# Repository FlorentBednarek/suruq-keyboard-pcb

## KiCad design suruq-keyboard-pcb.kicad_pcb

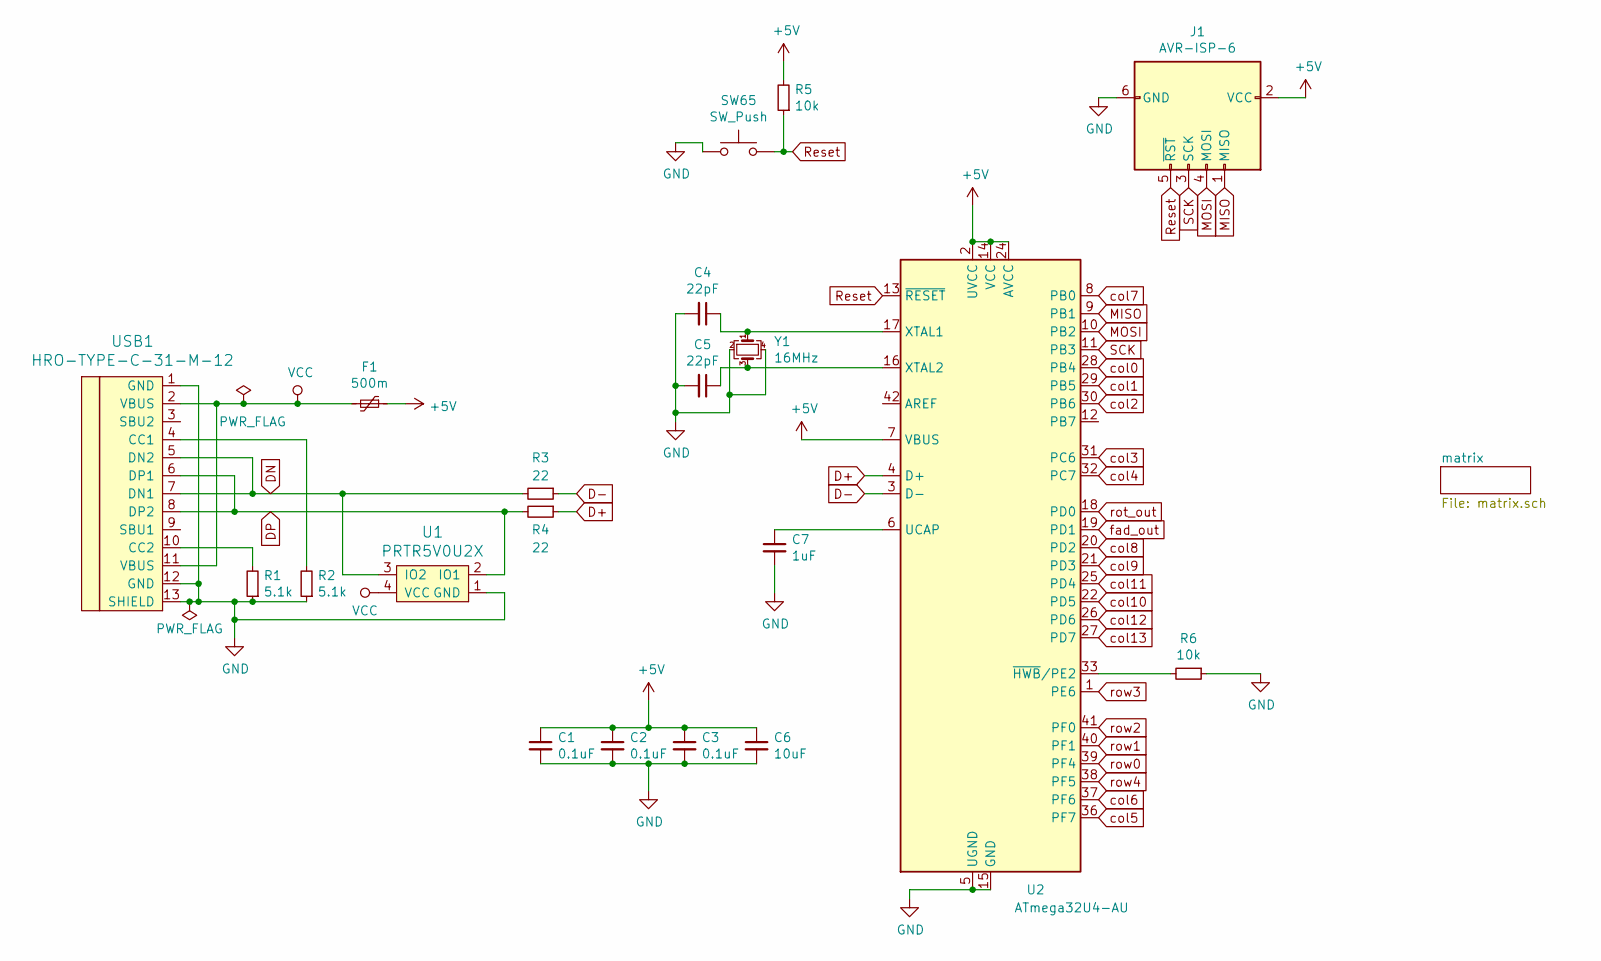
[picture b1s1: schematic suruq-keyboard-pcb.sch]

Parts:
C1, C2, C3: 0.1uF; C_0805_2012Metric_Pad1.15x1.40mm_HandSolder
C4, C5: 22pF; C_0805_2012Metric_Pad1.15x1.40mm_HandSolder
C6: 10uF; C_0805_2012Metric_Pad1.15x1.40mm_HandSolder
C7: 1uF; C_0805_2012Metric_Pad1.15x1.40mm_HandSolder
F1: 500m; Fuse_1206_3216Metric_Pad1.42x1.75mm_HandSolder
J1: AVR-ISP-6; Reset_Pretty-Mask
R1, R2: 5.1k; R_0805_2012Metric_Pad1.15x1.40mm_HandSolder
R3, R4: 22; R_0805_2012Metric_Pad1.15x1.40mm_HandSolder
R5, R6: 10k; R_0805_2012Metric_Pad1.15x1.40mm_HandSolder
SW65: SW_Push; SW_SPST_SKQG_WithStem
U1: PRTR5V0U2X; SOT143B
U2: ATmega32U4-AU; TQFP-44_10x10mm_P0.8mm
USB1: HRO-TYPE-C-31-M-12; HRO-TYPE-C-31-M-12-HandSoldering
Y1: 16MHz; Crystal_SMD_3225-4Pin_3.2x2.5mm_HandSoldering

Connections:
+5V: C1.1, C2.1, C3.1, C6.1, F1.1, J1.2 (VCC), R5.2, U2.2 (UVCC), U2.7 (VBUS), U2.14 (VCC), U2.24 (AVCC), U2.34 (VCC), U2.44 (AVCC); also elsewhere on the board
D+: R4.1, U2.4 (D+)
D-: R3.1, U2.3 (D-)
DN: R3.2, U1.3 (IO2), USB1.5 (DN2), USB1.7 (DN1)
DP: R4.2, U1.2 (IO1), USB1.6 (DP1), USB1.8 (DP2)
GND: C1.2, C2.2, C3.2, C4.2, C5.2, C6.2, C7.2, J1.6 (GND), R1.1, R2.1, R6.1, SW65.1, U1.1 (GND), U2.5 (UGND), U2.15 (GND), U2.23 (GND), U2.35 (GND), U2.43 (GND), USB1.1 (GND), USB1.12 (GND), USB1.13 (SHIELD), Y1.2, Y1.4; also elsewhere on the board
MISO: J1.1 (MISO), U2.9 (PB1)
MOSI: J1.4 (MOSI), U2.10 (PB2)
unnamed: C4.1, U2.17 (XTAL1), Y1.1
unnamed: C5.1, U2.16 (XTAL2), Y1.3
unnamed: C7.1, U2.6 (UCAP)
unnamed: R1.2, USB1.10 (CC2)
unnamed: R2.2, USB1.4 (CC1)
unnamed: R6.2, U2.33 (~HWB~/PE2)
Reset: J1.5 (~RST), R5.1, SW65.2, U2.13 (~RESET)
SCK: J1.3 (SCK), U2.11 (PB3)
VCC: F1.2, U1.4 (VCC), USB1.2 (VBUS), USB1.11 (VBUS)
col0: U2.28 (PB4); also elsewhere on the board
col1: U2.29 (PB5); also elsewhere on the board
col2: U2.30 (PB6); also elsewhere on the board
col3: U2.31 (PC6); also elsewhere on the board
col4: U2.32 (PC7); also elsewhere on the board
col5: U2.36 (PF7); also elsewhere on the board
col6: U2.37 (PF6); also elsewhere on the board
col7: U2.8 (PB0); also elsewhere on the board
col8: U2.20 (PD2); also elsewhere on the board
col9: U2.21 (PD3); also elsewhere on the board
col10: U2.22 (PD5); also elsewhere on the board
col11: U2.25 (PD4); also elsewhere on the board
col12: U2.26 (PD6); also elsewhere on the board
col13: U2.27 (PD7); also elsewhere on the board
fad_out: U2.19 (PD1); also elsewhere on the board
rot_out: U2.18 (PD0); also elsewhere on the board
row0: U2.39 (PF4); also elsewhere on the board
row1: U2.40 (PF1); also elsewhere on the board
row2: U2.41 (PF0); also elsewhere on the board
row3: U2.1 (PE6); also elsewhere on the board
row4: U2.38 (PF5); also elsewhere on the board

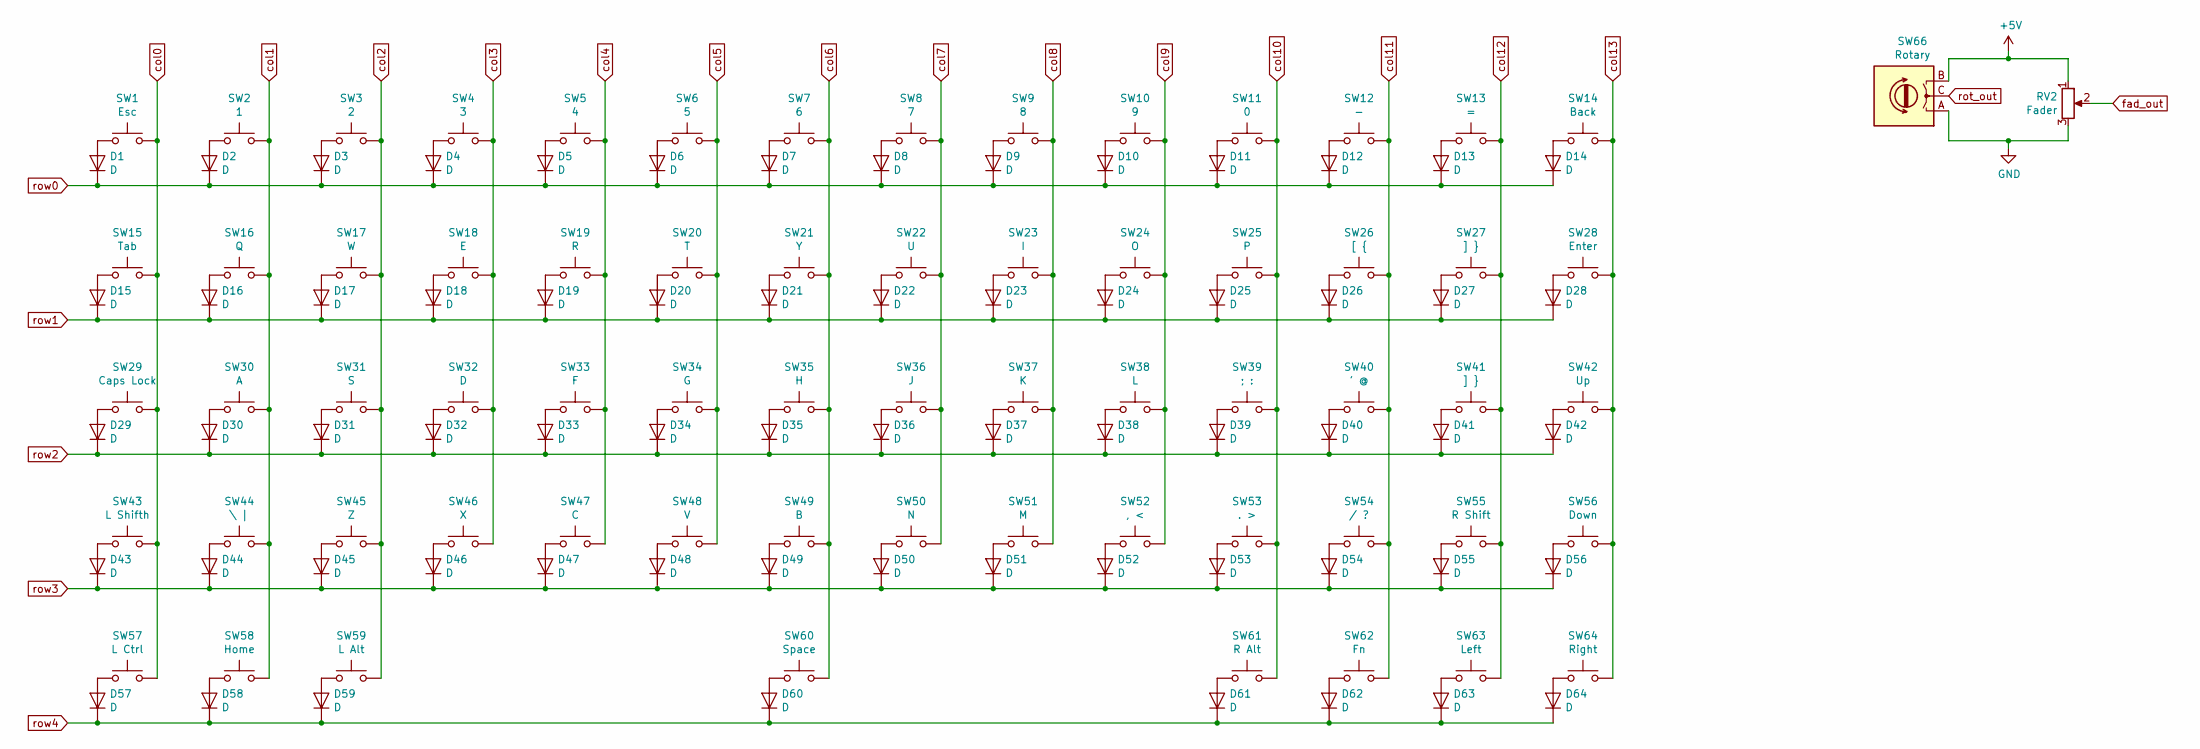
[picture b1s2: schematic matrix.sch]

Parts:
D1, D2, D3, D4, D5, D6, D7, D8, D9, D10, D11, D12, D13, D14, D15, D16, D17, D18, D19, D20, D21, D22, D23, D24, D25, D26, D27, D28, D29, D30, D31, D32, D33, D34, D35, D36, D37, D38, D39, D40, D41, D42, D43, D44, D45, D46, D47, D48, D49, D50, D51, D52, D53, D54, D55, D56, D57, D58, D59, D60, D61, D62, D63, D64: D; D_SOD-123
RV2: Fader; Potentiometer_Bourns_PTA4543_Single_Slide
SW1: Esc; SW_Cherry_MX_1.00u_PCB_NameSilk
SW2: 1; SW_Cherry_MX_1.00u_PCB_NameSilk
SW3: 2; SW_Cherry_MX_1.00u_PCB_NameSilk
SW4: 3; SW_Cherry_MX_1.00u_PCB_NameSilk
SW5: 4; SW_Cherry_MX_1.00u_PCB_NameSilk
SW6: 5; SW_Cherry_MX_1.00u_PCB_NameSilk
SW7: 6; SW_Cherry_MX_1.00u_PCB_NameSilk
SW8: 7; SW_Cherry_MX_1.00u_PCB_NameSilk
SW9: 8; SW_Cherry_MX_1.00u_PCB_NameSilk
SW10: 9; SW_Cherry_MX_1.00u_PCB_NameSilk
SW11: 0; SW_Cherry_MX_1.00u_PCB_NameSilk
SW12: -; SW_Cherry_MX_1.00u_PCB_NameSilk
SW13: =; SW_Cherry_MX_1.00u_PCB_NameSilk
SW14: Back; SW_Cherry_MX_2.00u_PCB_NameSilk
SW15: Tab; SW_Cherry_MX_1.50u_PCB_NameSilk
SW16: Q; SW_Cherry_MX_1.00u_PCB_NameSilk
SW17: W; SW_Cherry_MX_1.00u_PCB_NameSilk
SW18: E; SW_Cherry_MX_1.00u_PCB_NameSilk
SW19: R; SW_Cherry_MX_1.00u_PCB_NameSilk
SW20: T; SW_Cherry_MX_1.00u_PCB_NameSilk
SW21: Y; SW_Cherry_MX_1.00u_PCB_NameSilk
SW22: U; SW_Cherry_MX_1.00u_PCB_NameSilk
SW23: I; SW_Cherry_MX_1.00u_PCB_NameSilk
SW24: O; SW_Cherry_MX_1.00u_PCB_NameSilk
SW25: P; SW_Cherry_MX_1.00u_PCB_NameSilk
SW26: [ {; SW_Cherry_MX_1.00u_PCB_NameSilk
SW27, SW41: ] }; SW_Cherry_MX_1.00u_PCB_NameSilk
SW28: Enter; SW_Cherry_MX_ISOEnter_PCB_NameSilk
SW29: Caps Lock; SW_Cherry_MX_1.75u_PCB_NameSilk
SW30: A; SW_Cherry_MX_1.00u_PCB_NameSilk
SW31: S; SW_Cherry_MX_1.00u_PCB_NameSilk
SW32: D; SW_Cherry_MX_1.00u_PCB_NameSilk
SW33: F; SW_Cherry_MX_1.00u_PCB_NameSilk
SW34: G; SW_Cherry_MX_1.00u_PCB_NameSilk
SW35: H; SW_Cherry_MX_1.00u_PCB_NameSilk
SW36: J; SW_Cherry_MX_1.00u_PCB_NameSilk
SW37: K; SW_Cherry_MX_1.00u_PCB_NameSilk
SW38: L; SW_Cherry_MX_1.00u_PCB_NameSilk
SW39: ; :; SW_Cherry_MX_1.00u_PCB_NameSilk
SW40: ' @; SW_Cherry_MX_1.00u_PCB_NameSilk
SW42: Up; SW_Cherry_MX_1.00u_PCB_NameSilk
SW43: L Shifth; SW_Cherry_MX_1.25u_PCB_NameSilk
SW44: \\ |; SW_Cherry_MX_1.00u_PCB_NameSilk
SW45: Z; SW_Cherry_MX_1.00u_PCB_NameSilk
SW46: X; SW_Cherry_MX_1.00u_PCB_NameSilk
SW47: C; SW_Cherry_MX_1.00u_PCB_NameSilk
SW48: V; SW_Cherry_MX_1.00u_PCB_NameSilk
SW49: B; SW_Cherry_MX_1.00u_PCB_NameSilk
SW50: N; SW_Cherry_MX_1.00u_PCB_NameSilk
SW51: M; SW_Cherry_MX_1.00u_PCB_NameSilk
SW52: , <; SW_Cherry_MX_1.00u_PCB_NameSilk
SW53: . >; SW_Cherry_MX_1.00u_PCB_NameSilk
SW54: / ?; SW_Cherry_MX_1.00u_PCB_NameSilk
SW55: R Shift; SW_Cherry_MX_1.75u_PCB_NameSilk
SW56: Down; SW_Cherry_MX_1.00u_PCB_NameSilk
SW57: L Ctrl; SW_Cherry_MX_1.25u_PCB_NameSilk
SW58: Home; SW_Cherry_MX_1.25u_PCB_NameSilk
SW59: L Alt; SW_Cherry_MX_1.25u_PCB_NameSilk
SW60: Space; SW_Cherry_MX_6.25u_PCB_NameSilk
SW61: R Alt; SW_Cherry_MX_1.50u_PCB_NameSilk
SW62: Fn; SW_Cherry_MX_1.50u_PCB_NameSilk
SW63: Left; SW_Cherry_MX_1.00u_PCB_NameSilk
SW64: Right; SW_Cherry_MX_1.00u_PCB_NameSilk
SW66: Rotary; RotaryEncoder_Alps_EC11E_Vertical_H20mm

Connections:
+5V: RV2.1, SW66.B; also elsewhere on the board
GND: RV2.3, SW66.A; also elsewhere on the board
unnamed: D1.2 (A), SW1.1
unnamed: D2.2 (A), SW2.1
unnamed: D3.2 (A), SW3.1
unnamed: D4.2 (A), SW4.1
unnamed: D5.2 (A), SW5.1
unnamed: D6.2 (A), SW6.1
unnamed: D7.2 (A), SW7.1
unnamed: D8.2 (A), SW8.1
unnamed: D9.2 (A), SW9.1
unnamed: D10.2 (A), SW10.1
unnamed: D11.2 (A), SW11.1
unnamed: D12.2 (A), SW12.1
unnamed: D13.2 (A), SW13.1
unnamed: D14.2 (A), SW14.1
unnamed: D15.2 (A), SW15.1
unnamed: D16.2 (A), SW16.1
unnamed: D17.2 (A), SW17.1
unnamed: D18.2 (A), SW18.1
unnamed: D19.2 (A), SW19.1
unnamed: D20.2 (A), SW20.1
unnamed: D21.2 (A), SW21.1
unnamed: D22.2 (A), SW22.1
unnamed: D23.2 (A), SW23.1
unnamed: D24.2 (A), SW24.1
unnamed: D25.2 (A), SW25.1
unnamed: D26.2 (A), SW26.1
unnamed: D27.2 (A), SW27.1
unnamed: D28.2 (A), SW28.1
unnamed: D29.2 (A), SW29.1
unnamed: D30.2 (A), SW30.1
unnamed: D31.2 (A), SW31.1
unnamed: D32.2 (A), SW32.1
unnamed: D33.2 (A), SW33.1
unnamed: D34.2 (A), SW34.1
unnamed: D35.2 (A), SW35.1
unnamed: D36.2 (A), SW36.1
unnamed: D37.2 (A), SW37.1
unnamed: D38.2 (A), SW38.1
unnamed: D39.2 (A), SW39.1
unnamed: D40.2 (A), SW40.1
unnamed: D41.2 (A), SW41.1
unnamed: D42.2 (A), SW42.1
unnamed: D43.2 (A), SW43.1
unnamed: D44.2 (A), SW44.1
unnamed: D45.2 (A), SW45.1
unnamed: D46.2 (A), SW46.1
unnamed: D47.2 (A), SW47.1
unnamed: D48.2 (A), SW48.1
unnamed: D49.2 (A), SW49.1
unnamed: D50.2 (A), SW50.1
unnamed: D51.2 (A), SW51.1
unnamed: D52.2 (A), SW52.1
unnamed: D53.2 (A), SW53.1
unnamed: D54.2 (A), SW54.1
unnamed: D55.2 (A), SW55.1
unnamed: D56.2 (A), SW56.1
unnamed: D57.2 (A), SW57.1
unnamed: D58.2 (A), SW58.1
unnamed: D59.2 (A), SW59.1
unnamed: D60.2 (A), SW60.1
unnamed: D61.2 (A), SW61.1
unnamed: D62.2 (A), SW62.1
unnamed: D63.2 (A), SW63.1
unnamed: D64.2 (A), SW64.1
col0: SW1.2, SW15.2, SW29.2, SW43.2, SW57.2; also elsewhere on the board
col1: SW2.2, SW16.2, SW30.2, SW44.2, SW58.2; also elsewhere on the board
col2: SW3.2, SW17.2, SW31.2, SW45.2, SW59.2; also elsewhere on the board
col3: SW4.2, SW18.2, SW32.2, SW46.2; also elsewhere on the board
col4: SW5.2, SW19.2, SW33.2, SW47.2; also elsewhere on the board
col5: SW6.2, SW20.2, SW34.2, SW48.2; also elsewhere on the board
col6: SW7.2, SW21.2, SW35.2, SW49.2, SW60.2; also elsewhere on the board
col7: SW8.2, SW22.2, SW36.2, SW50.2; also elsewhere on the board
col8: SW9.2, SW23.2, SW37.2, SW51.2; also elsewhere on the board
col9: SW10.2, SW24.2, SW38.2, SW52.2; also elsewhere on the board
col10: SW11.2, SW25.2, SW39.2, SW53.2, SW61.2; also elsewhere on the board
col11: SW12.2, SW26.2, SW40.2, SW54.2, SW62.2; also elsewhere on the board
col12: SW13.2, SW27.2, SW41.2, SW55.2, SW63.2; also elsewhere on the board
col13: SW14.2, SW28.2, SW42.2, SW56.2, SW64.2; also elsewhere on the board
fad_out: RV2.2; also elsewhere on the board
rot_out: SW66.C; also elsewhere on the board
row0: D1.1 (K), D2.1 (K), D3.1 (K), D4.1 (K), D5.1 (K), D6.1 (K), D7.1 (K), D8.1 (K), D9.1 (K), D10.1 (K), D11.1 (K), D12.1 (K), D13.1 (K), D14.1 (K); also elsewhere on the board
row1: D15.1 (K), D16.1 (K), D17.1 (K), D18.1 (K), D19.1 (K), D20.1 (K), D21.1 (K), D22.1 (K), D23.1 (K), D24.1 (K), D25.1 (K), D26.1 (K), D27.1 (K), D28.1 (K); also elsewhere on the board
row2: D29.1 (K), D30.1 (K), D31.1 (K), D32.1 (K), D33.1 (K), D34.1 (K), D35.1 (K), D36.1 (K), D37.1 (K), D38.1 (K), D39.1 (K), D40.1 (K), D41.1 (K), D42.1 (K); also elsewhere on the board
row3: D43.1 (K), D44.1 (K), D45.1 (K), D46.1 (K), D47.1 (K), D48.1 (K), D49.1 (K), D50.1 (K), D51.1 (K), D52.1 (K), D53.1 (K), D54.1 (K), D55.1 (K), D56.1 (K); also elsewhere on the board
row4: D57.1 (K), D58.1 (K), D59.1 (K), D60.1 (K), D61.1 (K), D62.1 (K), D63.1 (K), D64.1 (K); also elsewhere on the board

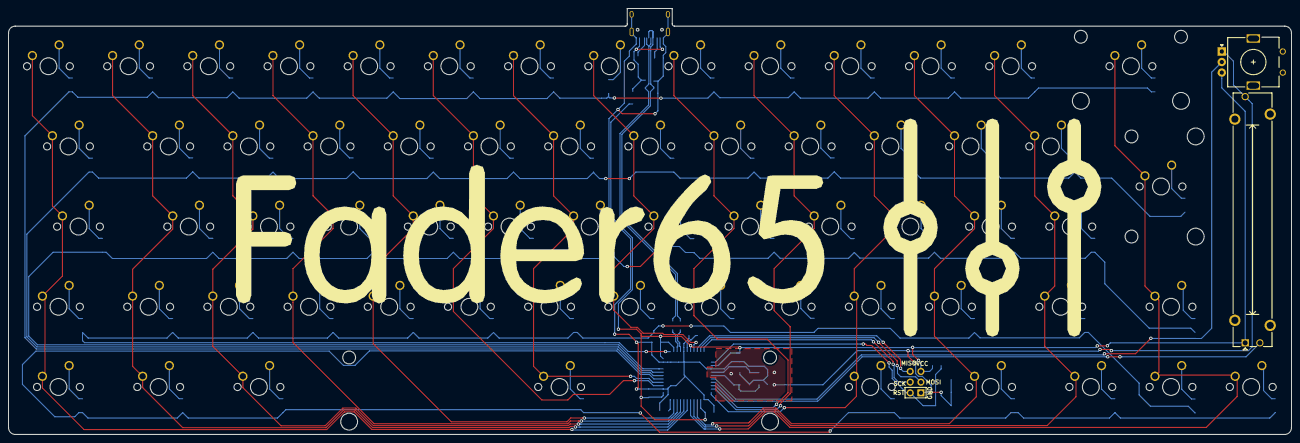
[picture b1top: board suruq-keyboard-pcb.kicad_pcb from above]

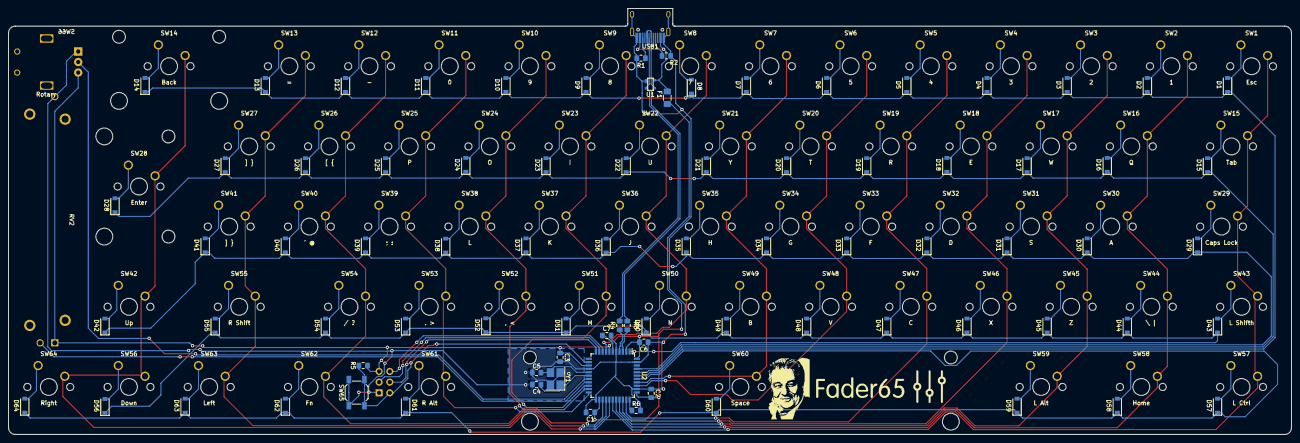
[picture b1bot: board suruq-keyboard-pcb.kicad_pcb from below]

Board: 2 copper layers, 304.8 x 101.2 mm, 152 parts (84 on the bottom side), 102 nets.

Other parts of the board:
logo: G***; logo
logo_small: G***; logo_small

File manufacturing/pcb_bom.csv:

Comment,Designator,Footprint,LCSC Part #
"0.1uF Unpolarized capacitor, small symbol","C1,C2,C3",C_0805_2012Metric_Pad1.15x1.40mm_HandSolder,C62912
"22pF Unpolarized capacitor, small symbol","C4,C5",C_0805_2012Metric_Pad1.15x1.40mm_HandSolder,C1804
"10uF Unpolarized capacitor, small symbol",C6,C_0805_2012Metric_Pad1.15x1.40mm_HandSolder,C95841
"1uF Unpolarized capacitor, small symbol",C7,C_0805_2012Metric_Pad1.15x1.40mm_HandSolder,C116352
D Diode,"D1,D2,D3,D4,D5,D6,D7,D8,D9,D10,D11,D12,D13,D15,D16,D17,D18,D19,D20,D21,D22,D23,D24,D25,D26,D27,D29,D30,D31,D32,D33,D34,D35,D36,D37,D38,D39,D40,D43,D44,D45,D46,D47,D48,D49,D50,D51,D52,D53,D55,D57,D58,D59,D60,D61,D62,D63,D42,D14,D56,D64,D28,D41,D54",D_SOD-123,C77987
"500m Resettable fuse, polymeric positive temperature coefficient, small symbol",F1,Fuse_1206_3216Metric_Pad1.42x1.75mm_HandSolder,C70069
"60@100MHz Ferrite bead, small symbol",FB1,L_0805_2012Metric_Pad1.15x1.40mm_HandSolder,C18305
"5.1k Resistor, small symbol","R1,R2",R_0805_2012Metric_Pad1.15x1.40mm_HandSolder,C84375
"22 Resistor, small symbol","R4,R3",R_0805_2012Metric_Pad1.15x1.40mm_HandSolder,C150390
"10k Resistor, small symbol","R6,R5",R_0805_2012Metric_Pad1.15x1.40mm_HandSolder,C84375
Fader Potentiometer,RV2,Potentiometer_Bourns_PTA4543_Single_Slide,
"SW_Push Push button switch, generic, two pins",SW65,SW_SPST_SKQG_WithStem,C221929
"Rotary Rotary encoder, dual channel, incremental quadrate outputs",SW66,RotaryEncoder_Alps_EC11E_Vertical_H20mm,
PRTR5V0U2X ,U1,SOT143B,C12333
"ATmega32U4-AU 16MHz, 16kB Flash, 1.25kB SRAM, 512B EEPROM, USB 2.0, TQFP-44",U2,TQFP-44_10x10mm_P0.8mm,C44854
HRO-TYPE-C-31-M-12 ,USB1,HRO-TYPE-C-31-M-12-HandSoldering,C165948
"16MHz Four pin crystal, GND on pins 2 and 4, small symbol",Y1,Crystal_SMD_3225-4Pin_3.2x2.5mm_HandSoldering,C255909

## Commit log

2020-12-20 create project
2020-12-20 add submodule
2020-12-20 link submodule to kicad project
2020-12-21 MCU and Switches Matrix electrical schema
2020-12-25 change layout and matrix
2021-01-05 pcb layout routing WIP
2021-01-06 routing gauche et MCU
2021-01-06 fin routing
2021-01-13 backup au cas ou
2021-01-13 add silk screen, Fader65
2021-01-13 create gerber file and BOM
